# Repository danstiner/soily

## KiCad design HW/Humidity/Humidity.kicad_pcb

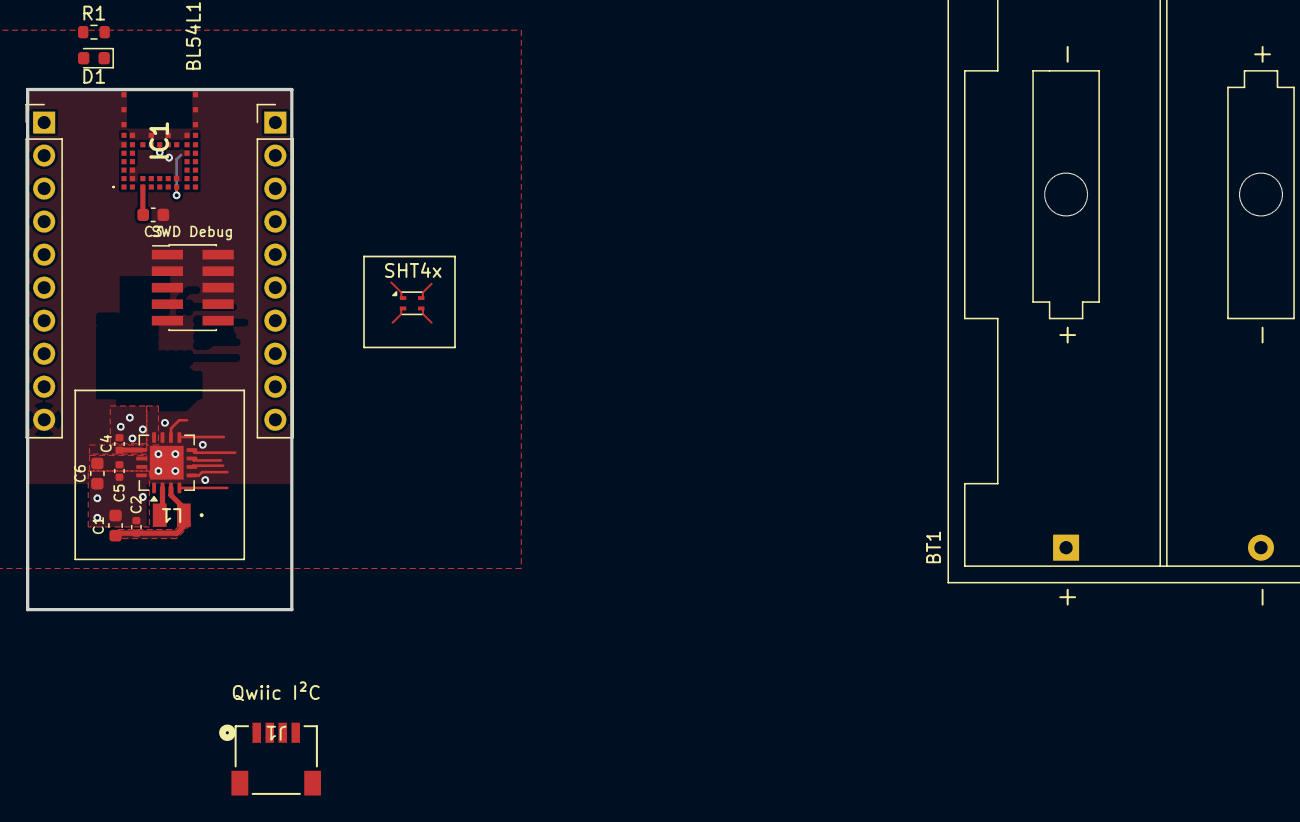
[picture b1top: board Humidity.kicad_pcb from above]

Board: 2 copper layers, 20.3 x 40.0 mm, 17 parts (0 on the bottom side), 15 nets.

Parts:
BT1: Battery; BatteryHolder_Keystone_2462_2xAA
C1, C6: 22μF; C_0603_1608Metric
C2, C5: 10nF; C_0402_1005Metric
C3: 10uF; C_0603_1608Metric
C4: 2.2μF; C_0402_1005Metric
D1: PWRLED; LED_0603_1608Metric
IC1: nrf54L 453-00223R; 45300223R
J1: Conn_Qwiic; CONN_SM04B-SRSS-TB_JST
J2: Conn_ARM_JTAG_SWD_10; PinHeader_2x05_P1.27mm_Vertical_SMD
J3, J4: Conn_01x10_Pin; PinHeader_1x10_P2.54mm_Vertical
L1: 2.2μH; IND_CIGT2016_SAM
R1: 2K; R_0603_1608Metric
U2: nPM2100-QEXX; UQFN-16-1EP_4x4mm_P0.65mm_EP2.6x2.6mm
U3: SHT4x; Sensirion_DFN-4_1.5x1.5mm_P0.8mm_SHT4x_NoCentralPad

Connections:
/LED: IC1.21 (P1.10), J4.5, R1.1
/NRESET: IC1.32 (NRESET), J2.10 (~RESET), J4.1
/PG/RESET: IC1.45 (P2.04), U2.10 (PG/RESET)
/SCL: IC1.17 (P1.04/AIN0/CLK), J1.4, J4.7, U2.7 (SCL), U3.2 (SCL)
/SDA: IC1.18 (P1.14), J1.3, J4.6, U2.6 (SDA), U3.1 (SDA)
/SW: L1.2, U2.2 (SW)
/SWDCLK: IC1.25 (SWDCLK), J2.4 (SWCLK/TCK), J4.3
/SWDIO: IC1.27 (SWDIO), J2.2 (SWDIO/TMS), J4.2
/SWO: IC1.13 (P2.02), J2.6 (SWO/TDO), J4.4
/VBAT: BT1.1 (+), C1.1, C2.1, L1.1, U2.3 (VBAT)
/VINT: C5.1, C6.1, U2.14 (VINT), U2.15 (VINT)
GND: BT1.2 (-), C1.2, C2.2, C3.2, C4.2, C5.2, C6.2, D1.1 (K), IC1.4 (GND_1), IC1.14 (GND_2), IC1.24 (GND_3), IC1.28 (GND_4), IC1.31 (GND_5), IC1.34 (GND_6), IC1.36 (GND_7), IC1.39 (GND_8), IC1.44 (P2.03), IC1.46 (GND_9), IC1.47 (GND_10), IC1.48 (GND_11), IC1.49 (GND_12), IC1.50 (GND_13), IC1.51 (GND_14), J1.1, J1.5 (MT1), J1.6 (MT2), J2.3 (GND), J2.5 (GND), J2.9 (GNDDetect), J3.10, U2.11 (AVSS2), U2.16 (PVSS), U2.17 (EP), U3.4 (VSS)
unnamed: D1.2 (A), R1.2
VDD: C3.1, C4.1, IC1.5 (VDD_NRF), J2.1 (VTref), U2.13 (VOUT)
VDDSW: J1.2, U2.12 (VOUTLDO), U3.3 (VDD)

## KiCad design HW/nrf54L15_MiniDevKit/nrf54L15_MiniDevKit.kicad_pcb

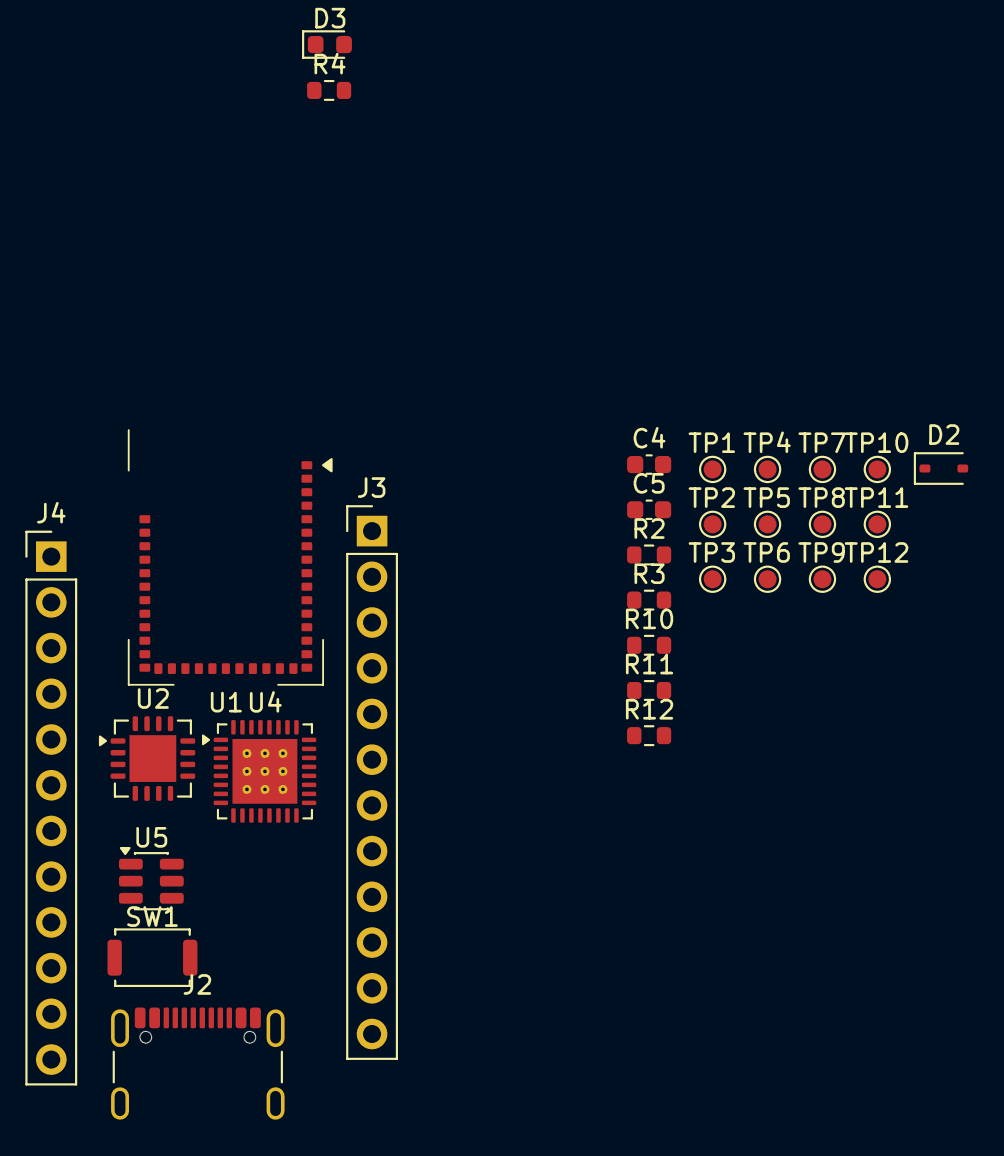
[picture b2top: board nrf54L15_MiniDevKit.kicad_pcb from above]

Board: 2 copper layers, 30 parts (0 on the bottom side), 14 nets, no tracks yet.

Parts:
C4, C5: 1u; C_0603_1608Metric
D2: B0520WS-7-F; D_SOD-323
D3: PWRLED; LED_0603_1608Metric
J2: USB4105-GF-A; USB_C_Receptacle_GCT_USB4105-xx-A_16P_TopMnt_Horizontal
J3, J4: Conn_Breadboard; PinHeader_1x12_P2.54mm_Vertical
R2, R3: 5.1k; R_0603_1608Metric
R4: 680; R_0603_1608Metric
R10: 60; R_0603_1608Metric
R11, R12: 10; R_0603_1608Metric
SW1: Reset; SW_Push_SPST_NO_Alps_SKRK
TP1: 3.3V; TestPoint_Pad_D1.0mm
TP2: GND; TestPoint_Pad_D1.0mm
TP3: BOOT; TestPoint_Pad_D1.0mm
TP4: RST; TestPoint_Pad_D1.0mm
TP5: UART_TX; TestPoint_Pad_D1.0mm
TP6: UART_RX; TestPoint_Pad_D1.0mm
TP7: SCL; TestPoint_Pad_D1.0mm
TP8: SDA; TestPoint_Pad_D1.0mm
TP9: SOIL_A; TestPoint_Pad_D1.0mm
TP10: EOH; TestPoint_Pad_D1.0mm
TP11: FDC_OFF; TestPoint_Pad_D1.0mm
TP12: SOIL_B; TestPoint_Pad_D1.0mm
U1: BL54L15-453-000xxx; BL54Lxx-LGA-39_14x10mm
U2: nPM2100-QEXX; UQFN-16-1EP_4x4mm_P0.65mm_EP2.6x2.6mm
U4: nPM1300-QEXX; QFN-32-1EP_5x5mm_P0.5mm_EP3.6x3.6mm_ThermalVias
U5: USBLC6-2SC6; SOT-23-6

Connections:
+3.3V: C5.1, J4.4, R4.1, TP1.1
/D+: J2.A6 (D+), J2.B6 (D+), U5.3 (I/O2)
/D-: J2.A7 (D-), J2.B7 (D-), U5.1 (I/O1)
/EOH: J4.8, TP10.1
/RESET: SW1.1, TP4.1
/SCL: J4.7, TP7.1
/SDA: J4.6, TP8.1
/USB_VBUS: D2.2 (A), J2.A4 (VBUS), J2.A9 (VBUS), J2.B4 (VBUS), J2.B9 (VBUS), U5.5 (VBUS)
GND: C4.2, C5.2, D3.1 (K), J2.A1 (GND), J2.A12 (GND), J2.B1 (GND), J2.B12 (GND), J2.S1 (SHIELD), J4.5, R2.1, R3.2, R10.2, R11.2, R12.2, SW1.2, TP2.1, U1.1 (VSS), U1.16 (VSS), U1.27 (VSS), U1.39 (VSS), U2.11 (AVSS2), U2.16 (PVSS), U2.17 (EP), U4.33 (AVSS), U5.2 (GND)
unnamed: C4.1, D2.1 (K)
unnamed: D3.2 (A), R4.2
unnamed: J2.A5 (CC1), R2.2
unnamed: J2.B5 (CC2), R3.1
unnamed: U2.14 (VINT), U2.15 (VINT)

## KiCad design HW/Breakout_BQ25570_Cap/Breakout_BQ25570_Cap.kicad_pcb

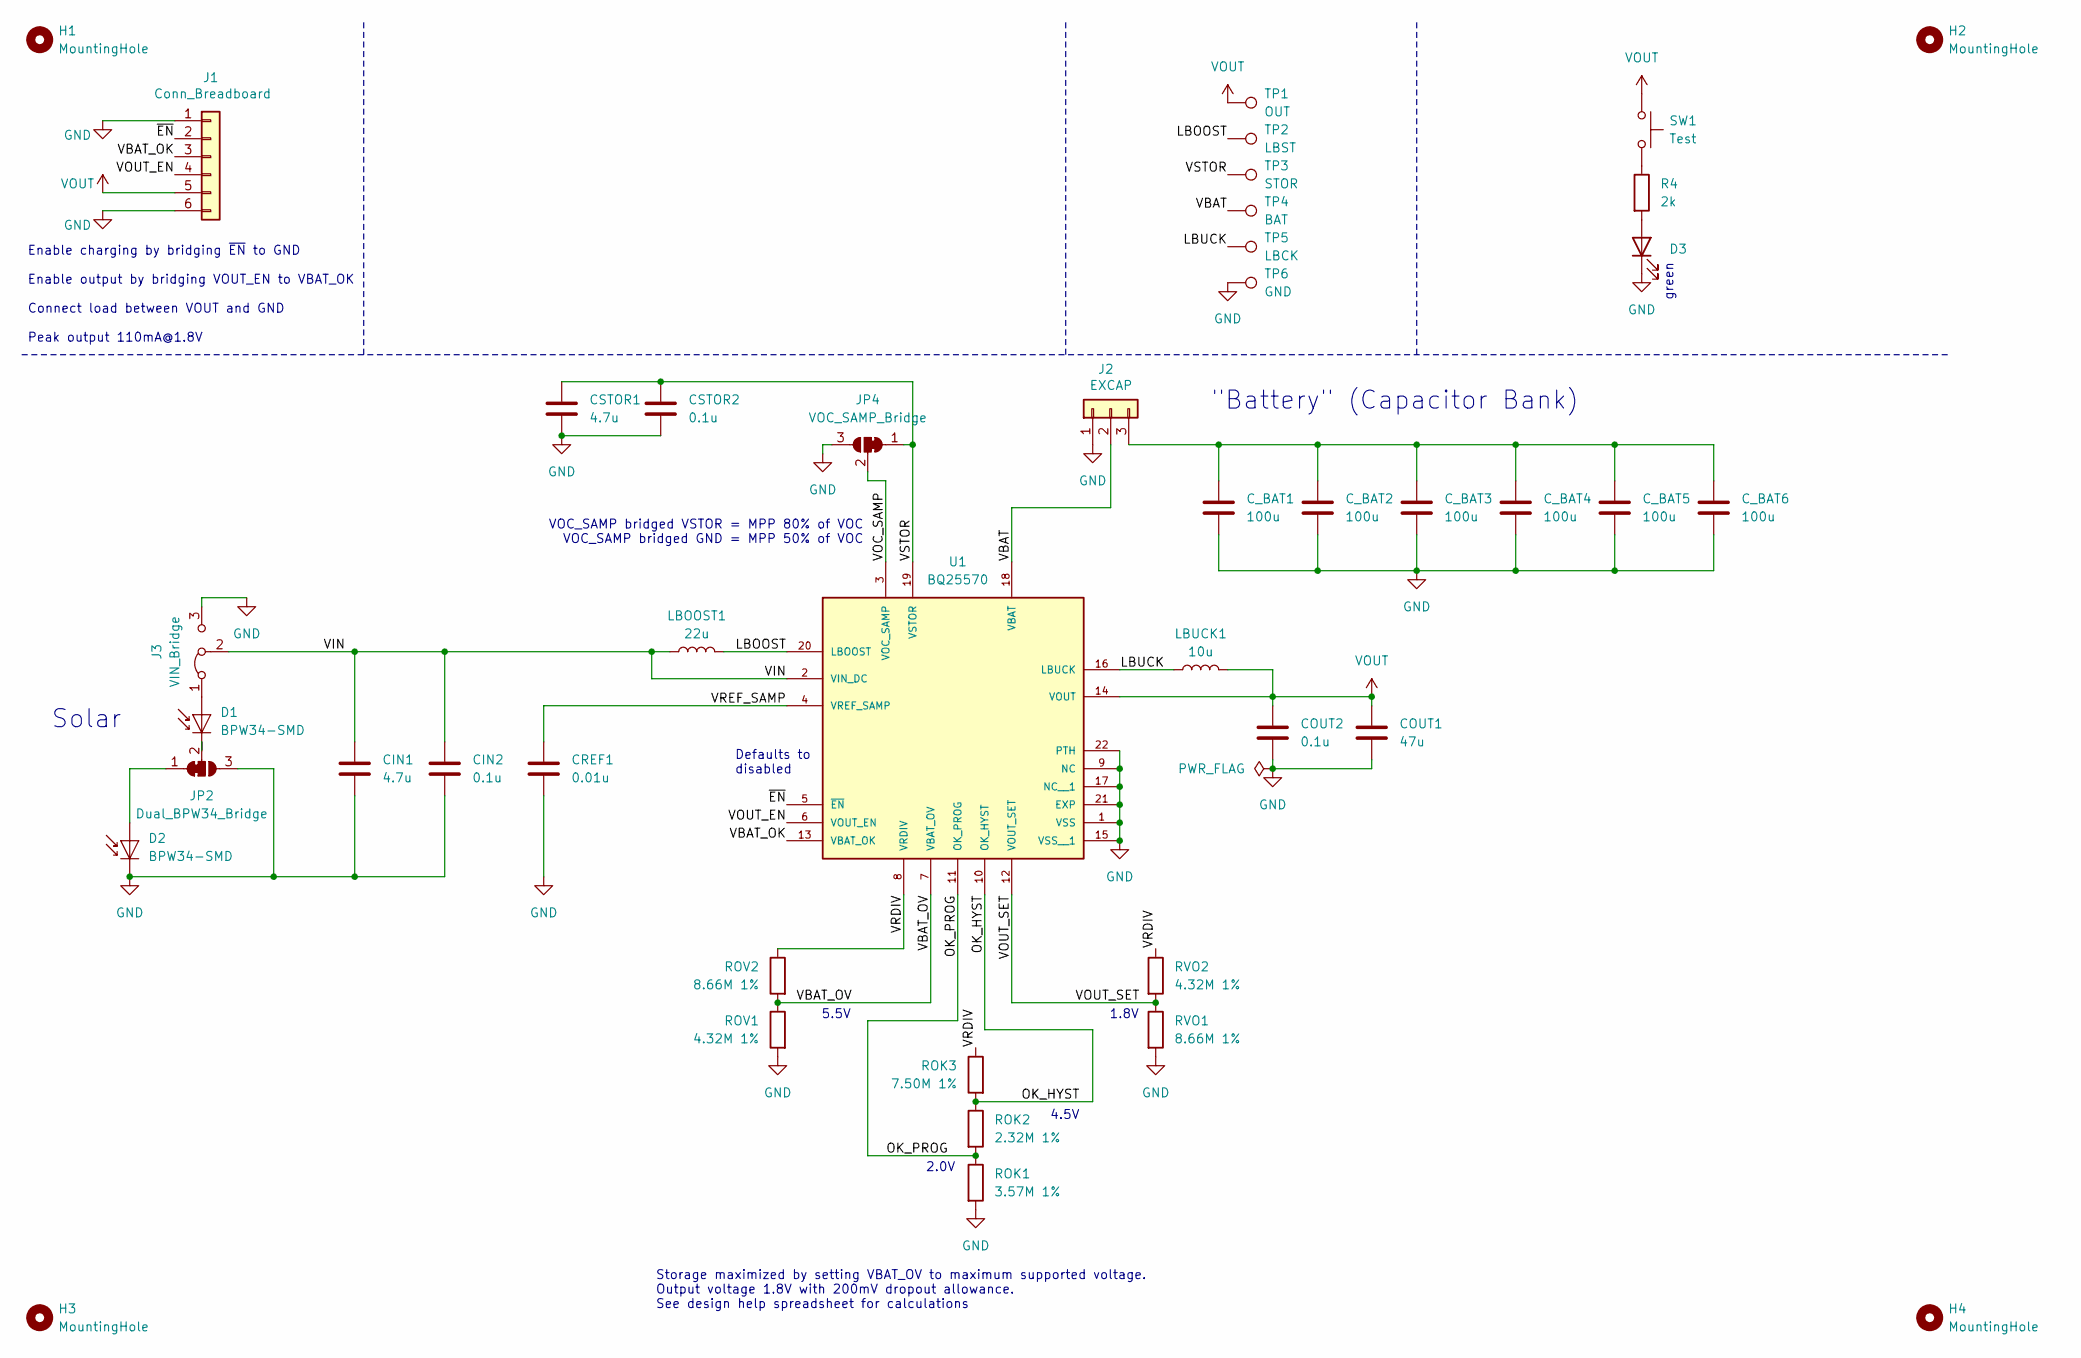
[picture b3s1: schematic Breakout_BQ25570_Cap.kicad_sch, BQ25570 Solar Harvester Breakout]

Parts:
CIN1: 4.7u; C_0603_1608Metric
CIN2: 0.1u; C_0402_1005Metric
COUT1: 47u; C_0603_1608Metric
COUT2: 0.1u; C_0402_1005Metric
CREF1: 0.01u; C_0402_1005Metric; Digikey Part Number 1276-1028-1-ND
CSTOR1: 4.7u; C_0603_1608Metric
CSTOR2: 0.1u; C_0402_1005Metric
C_BAT1: 100u; C_1206_3216Metric; Digikey Part Number 490-GRM31CR61A107MEA8LCT-ND
C_BAT2, C_BAT3, C_BAT4, C_BAT5, C_BAT6: 100u; C_1206_3216Metric
D1, D2: BPW34-SMD; Osram_BPW34S-SMD
D3: PWRLED; LED_0603_1608Metric
H1, H2, H3, H4: MountingHole; MountingHole_2.5mm_Plated
J1: Conn_Breadboard; PinHeader_1x06_P2.54mm_Vertical
J2: EXCAP; PinHeader_1x03_P2.54mm_Vertical
J3: VIN_Bridge; PinHeader_1x03_P2.54mm_Vertical
JP2: Dual_BPW34_Bridge; SolderJumper-3_P1.3mm_Bridged12_RoundedPad1.0x1.5mm
JP4: VOC_SAMP_Bridge; SolderJumper-3_P1.3mm_Bridged12_RoundedPad1.0x1.5mm
LBOOST1: 22u; L_Bourns-SRN4018; Digikey Part Number 118-SRN2012T-220KCT-ND
LBUCK1: 10u; L_1008_2520Metric; Digikey Part Number 490-10563-1-ND
R4: 2k; R_0603_1608Metric; Digikey Part Number 13-RC0603FR-101KLCT-ND
ROK1: 3.57M 1%; R_0603_1608Metric
ROK2: 2.32M 1%; R_0603_1608Metric
ROK3: 7.50M 1%; R_0603_1608Metric
ROV1: 4.32M 1%; R_0603_1608Metric
ROV2: 8.66M 1%; R_0603_1608Metric
RVO1: 8.66M 1%; R_0603_1608Metric
RVO2: 4.32M 1%; R_0603_1608Metric
SW1: Test; SW_Push_SPST_NO_Alps_SKRK; Part Number SKRKAHE020; Digikey Part Number 4809-SKRKAHE020CT-ND
TP1: OUT; TestPoint_Pad_D1.0mm
TP2: LBST; TestPoint_Pad_D1.0mm
TP3: STOR; TestPoint_Pad_D1.0mm
TP4: BAT; TestPoint_Pad_D1.0mm
TP5: LBCK; TestPoint_Pad_D1.0mm
TP6: GND; TestPoint_Pad_D1.0mm
U1: BQ25570; QFN50P350X350X100-21N; PARTREV G

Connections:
/LBOOST: LBOOST1.2, TP2.1, U1.20 (LBOOST)
/LBUCK: LBUCK1.1, TP5.1, U1.16 (LBUCK)
/OK_HYST: ROK2.1, ROK3.2, U1.10 (OK_HYST)
/OK_PROG: ROK1.1, ROK2.2, U1.11 (OK_PROG)
/VBAT: J2.2, TP4.1, U1.18 (VBAT)
/VBAT_OK: J1.3, U1.13 (VBAT_OK)
/VBAT_OV: ROV1.1, ROV2.2, U1.7 (VBAT_OV)
/VIN: CIN1.1, CIN2.1, J3.2 (C), LBOOST1.1, U1.2 (VIN_DC)
/VOC_SAMP: JP4.2 (C), U1.3 (VOC_SAMP)
/VOUT_EN: J1.4, U1.6 (VOUT_EN)
/VOUT_SET: RVO1.1, RVO2.2, U1.12 (VOUT_SET)
/VRDIV: ROK3.1, ROV2.1, RVO2.1, U1.8 (VRDIV)
/VREF_SAMP: CREF1.1, U1.4 (VREF_SAMP)
/VSTOR: CSTOR1.1, CSTOR2.1, JP4.1 (A), TP3.1, U1.19 (VSTOR)
/~EN: J1.2, U1.5 (~EN)
GND: CIN1.2, CIN2.2, COUT1.2, COUT2.2, CREF1.2, CSTOR1.2, CSTOR2.2, C_BAT1.2, C_BAT2.2, C_BAT3.2, C_BAT4.2, C_BAT5.2, C_BAT6.2, D2.1 (K), D3.1 (K), J1.1, J1.6, J2.1, J3.3 (B), JP2.3 (B), JP4.3 (B), ROK1.2, ROV1.2, RVO1.2, TP6.1, U1.1 (VSS), U1.9 (NC), U1.15 (VSS__1), U1.17 (NC__1), U1.21 (EXP), U1.22 (PTH), U1.23 (PTH), U1.24 (PTH), U1.25 (PTH), U1.26 (PTH)
unnamed: D1.2 (A), J3.1 (A)
unnamed: D1.1 (K), JP2.2 (C)
unnamed: D2.2 (A), JP2.1 (A)
unnamed: D3.2 (A), R4.2
unnamed: C_BAT1.1, C_BAT2.1, C_BAT3.1, C_BAT4.1, C_BAT5.1, C_BAT6.1, J2.3
unnamed: R4.1, SW1.2
VOUT: COUT1.1, COUT2.1, J1.5, LBUCK1.2, SW1.1, TP1.1, U1.14 (VOUT)

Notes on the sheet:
1.8V
Solar
Defaults to disabled
VOC_SAMP bridged VSTOR = MPP 80% of VOC VOC_SAMP bridged GND = MPP 50% of VOC
Enable charging by bridging ~{EN} to GND Enable output by bridging VOUT_EN to VBAT_OK Connect load between VOUT and GND Peak output 110mA@1.8V
2.0V
green
"Battery" (Capacitor Bank)
Storage maximized by setting VBAT_OV to maximum supported voltage. Output voltage 1.8V with 200mV dropout allowance. See design help spreadsheet for calculations
5.5V
4.5V

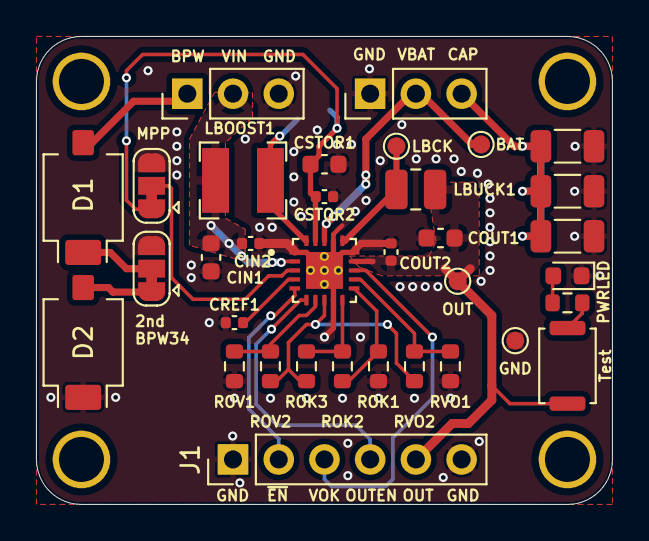
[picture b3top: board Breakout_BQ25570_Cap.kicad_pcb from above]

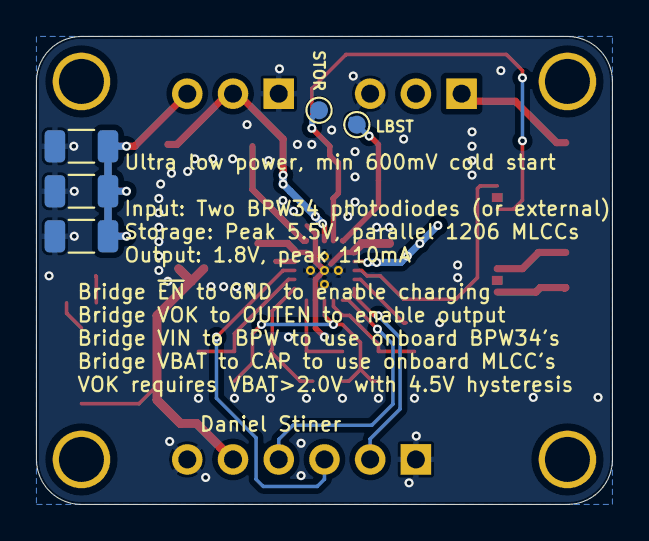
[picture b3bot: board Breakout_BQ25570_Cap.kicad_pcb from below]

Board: 2 copper layers, 32.0 x 26.0 mm, 43 parts (5 on the bottom side), 23 nets.

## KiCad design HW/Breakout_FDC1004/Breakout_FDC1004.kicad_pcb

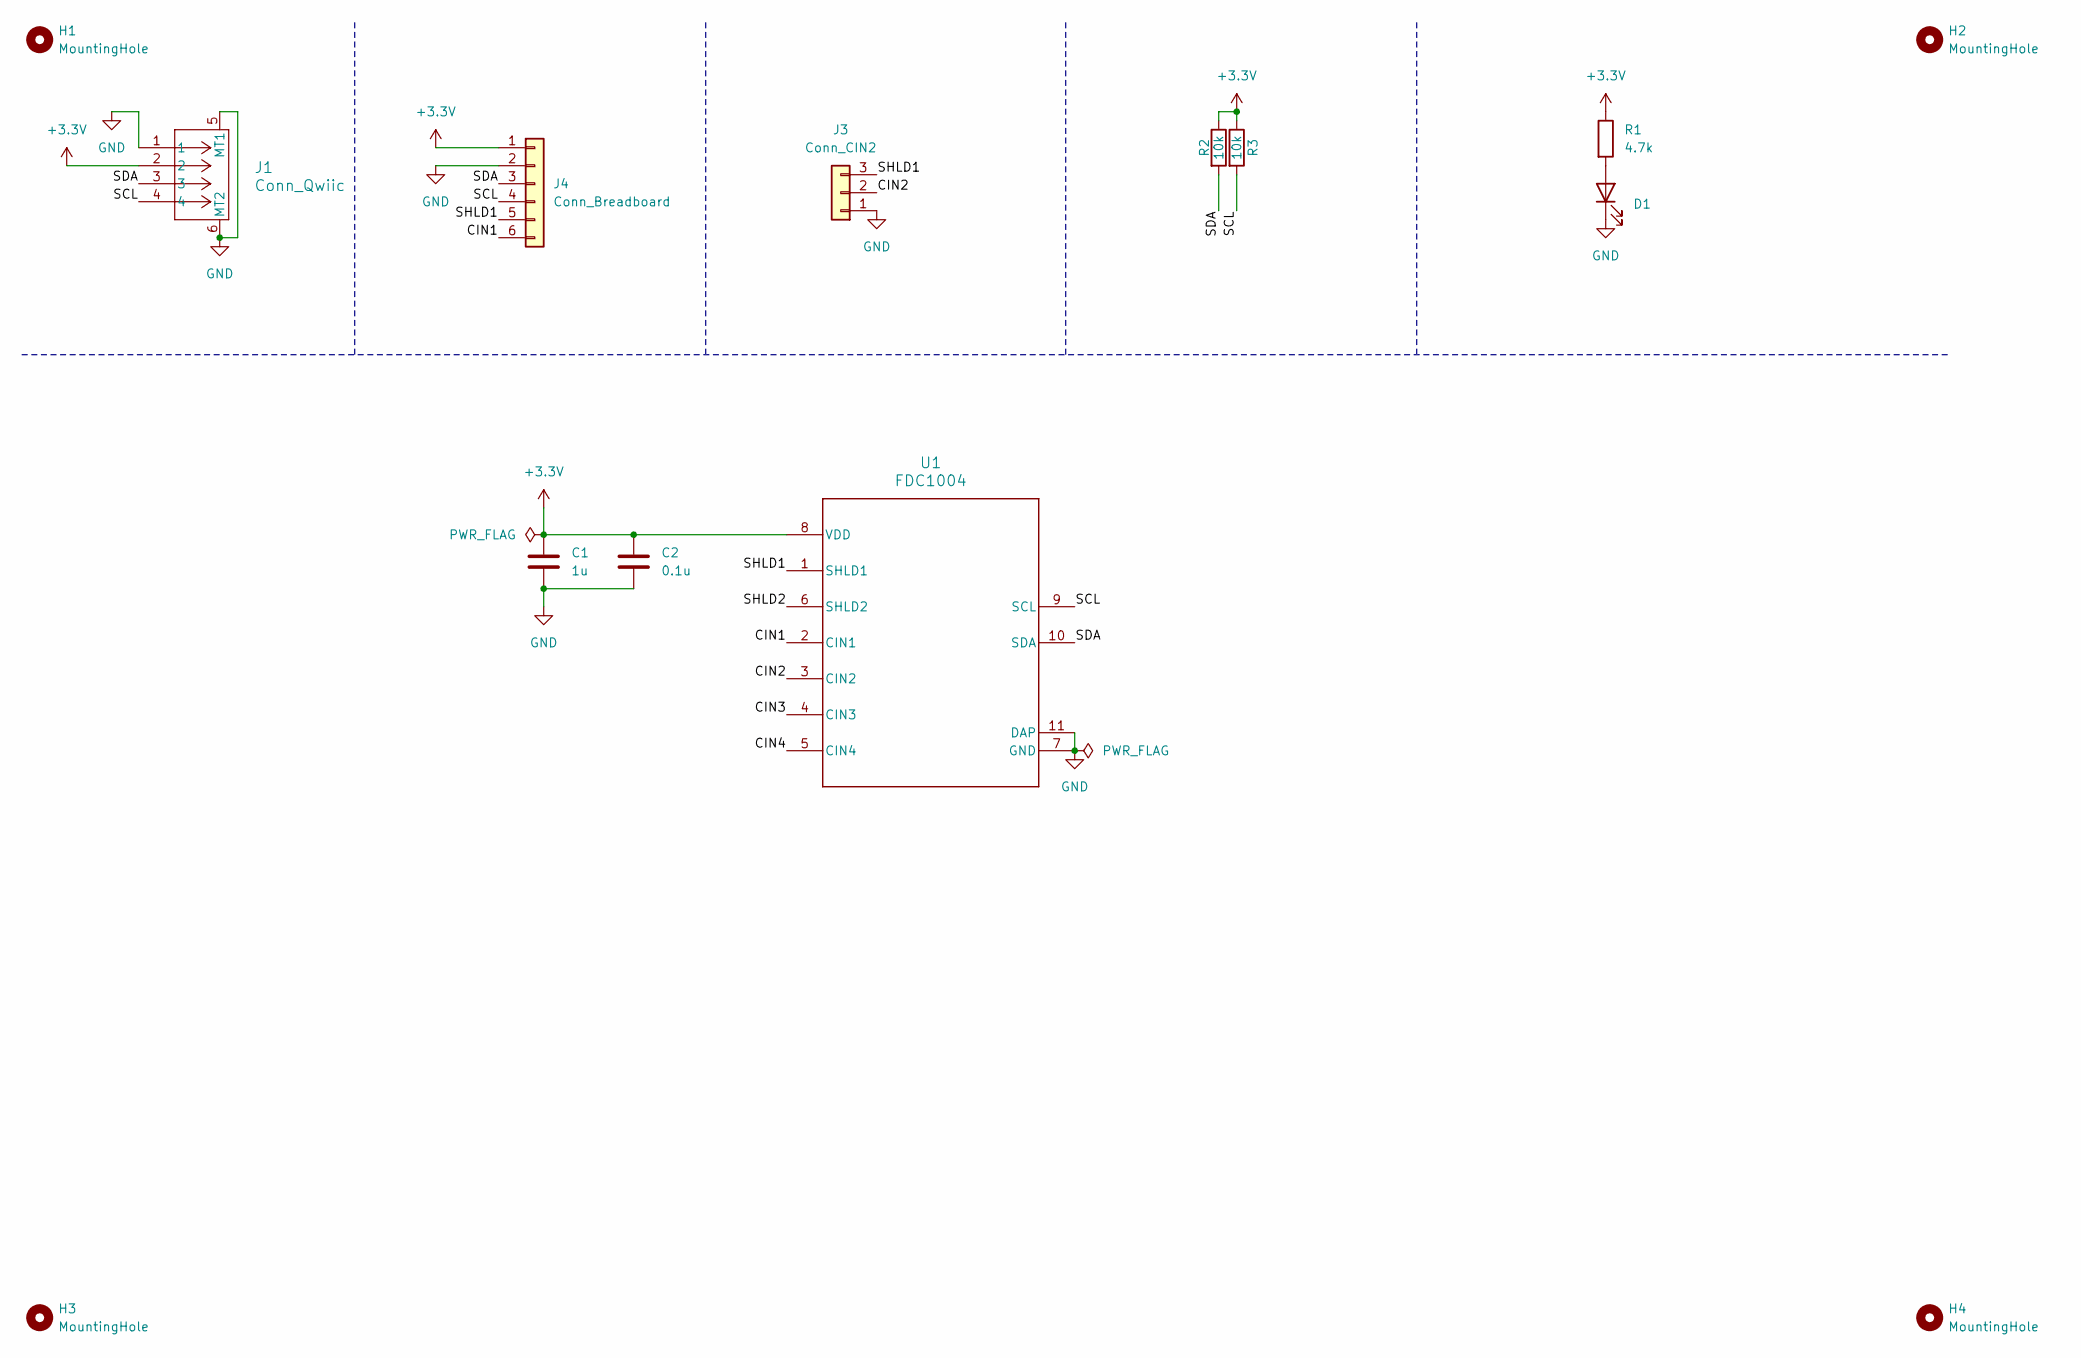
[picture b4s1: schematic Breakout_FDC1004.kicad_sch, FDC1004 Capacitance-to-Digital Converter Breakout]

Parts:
C1: 1u; C_0603_1608Metric
C2: 0.1u; C_0402_1005Metric
D1: PWRLED; LED_0603_1608Metric
H1, H2, H3, H4: MountingHole; MountingHole_2.5mm_Plated
J1: Conn_Qwiic; CONN_SM04B-SRSS-TB_JST
J3: Conn_CIN2; PinHeader_1x03_P2.54mm_Vertical
J4: Conn_Breadboard; PinHeader_1x06_P2.54mm_Vertical
R1: 4.7k; R_0603_1608Metric
R2, R3: 10k; R_0603_1608Metric; Digikey Part Number 311-10.0KHRCT-ND
U1: FDC1004; DSC0010B

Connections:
+3.3V: C1.1, C2.1, J1.2, J4.1, R1.1, R2.1, R3.1, U1.8 (VDD)
/CIN1: J4.6, U1.2 (CIN1)
/CIN2: J3.2, U1.3 (CIN2)
/CIN3: U1.4 (CIN3)
/CIN4: U1.5 (CIN4)
/SCL: J1.4, J4.4, R3.2, U1.9 (SCL)
/SDA: J1.3, J4.3, R2.2, U1.10 (SDA)
/SHLD1: J3.3, J4.5, U1.1 (SHLD1)
/SHLD2: U1.6 (SHLD2)
GND: C1.2, C2.2, D1.1 (K), J1.1, J1.5 (MT1), J1.6 (MT2), J3.1, J4.2, U1.7 (GND), U1.11 (DAP), U1.V (VIA)
unnamed: D1.2 (A), R1.2

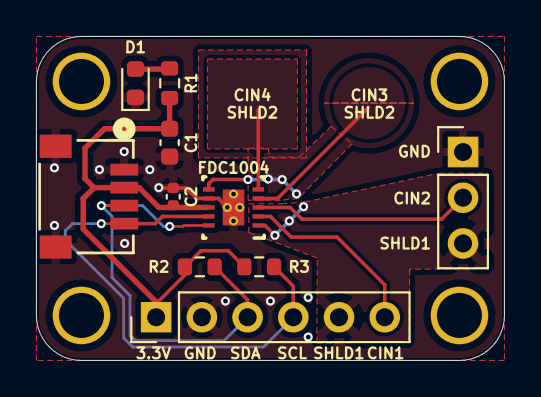
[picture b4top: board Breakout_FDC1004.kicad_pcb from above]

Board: 2 copper layers, 26.0 x 18.0 mm, 14 parts (0 on the bottom side), 8 nets.

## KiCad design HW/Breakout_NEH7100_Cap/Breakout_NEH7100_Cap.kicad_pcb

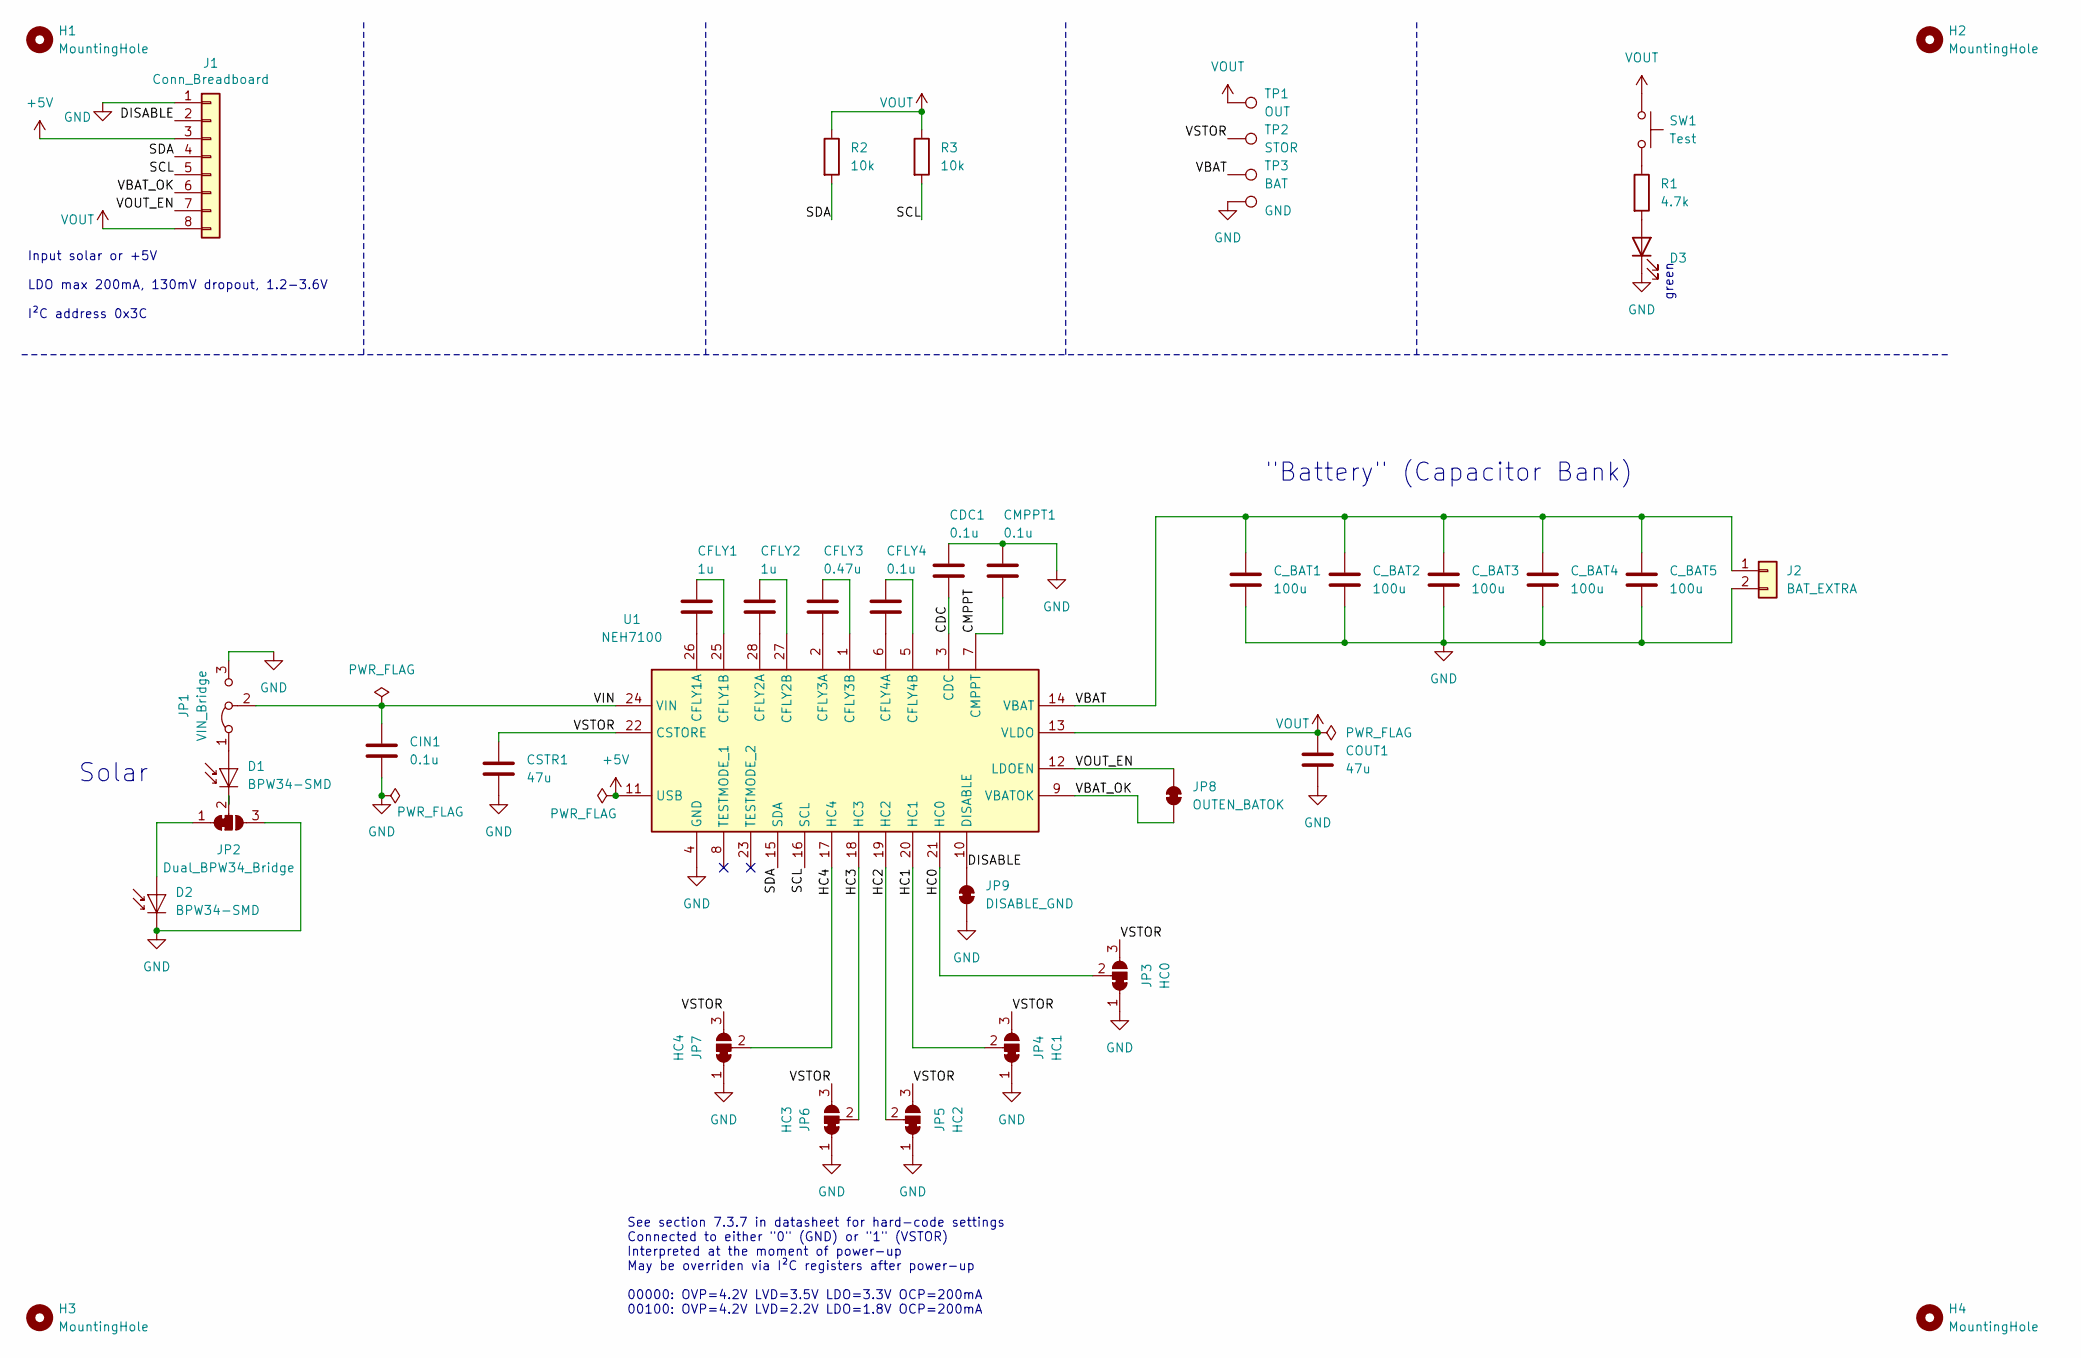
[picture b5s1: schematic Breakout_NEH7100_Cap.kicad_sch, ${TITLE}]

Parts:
CDC1: 0.1u; C_0402_1005Metric
CFLY1, CFLY2: 1u; C_0402_1005Metric
CFLY3: 0.47u; C_0402_1005Metric
CFLY4: 0.1u; C_0402_1005Metric
CIN1: 0.1u; C_0402_1005Metric
CMPPT1: 0.1u; C_0402_1005Metric
COUT1: 47u; C_0603_1608Metric
CSTR1: 47u; C_0603_1608Metric; Digikey Part Number 1276-1028-1-ND
C_BAT1: 100u; C_1206_3216Metric; Digikey Part Number 490-GRM31CR61A107MEA8LCT-ND
C_BAT2, C_BAT3, C_BAT4, C_BAT5: 100u; C_1206_3216Metric
D1, D2: BPW34-SMD; Osram_BPW34S-SMD
D3: PWRLED; LED_0603_1608Metric
H1, H2, H3, H4: MountingHole; MountingHole_2.5mm_Plated
J1: Conn_Breadboard; PinHeader_1x08_P2.54mm_Vertical
J2: BAT_EXTRA; PinHeader_1x02_P2.54mm_Vertical
JP1: VIN_Bridge; PinHeader_1x03_P2.54mm_Vertical
JP2: Dual_BPW34_Bridge; SolderJumper-3_P1.3mm_Bridged12_RoundedPad1.0x1.5mm
JP3: HC0; SolderJumper-3_P1.3mm_Bridged12_RoundedPad1.0x1.5mm
JP4: HC1; SolderJumper-3_P1.3mm_Bridged12_RoundedPad1.0x1.5mm
JP5: HC2; SolderJumper-3_P1.3mm_Bridged12_RoundedPad1.0x1.5mm
JP6: HC3; SolderJumper-3_P1.3mm_Bridged12_RoundedPad1.0x1.5mm
JP7: HC4; SolderJumper-3_P1.3mm_Bridged12_RoundedPad1.0x1.5mm
JP8: OUTEN_BATOK; SolderJumper-2_P1.3mm_Bridged_RoundedPad1.0x1.5mm
JP9: DISABLE_GND; SolderJumper-2_P1.3mm_Bridged_RoundedPad1.0x1.5mm
R1: 4.7k; R_0603_1608Metric; Digikey Part Number 13-RC0603FR-101KLCT-ND
R2, R3: 10k; R_0603_1608Metric
SW1: Test; SW_Push_SPST_NO_Alps_SKRK; Part Number SKRKAHE020; Digikey Part Number 4809-SKRKAHE020CT-ND
TP1: OUT; TestPoint_Pad_D1.0mm
TP2: STOR; TestPoint_Pad_D1.0mm
TP3: BAT; TestPoint_Pad_D1.0mm
TP6: GND; TestPoint_Pad_D1.0mm
U1: NEH7100; QFN40P400X400X90-29N-D; Mouser Part Number 771-NEH7100BUHP

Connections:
+5V: J1.3, U1.11 (USB)
/CDC: CDC1.2, U1.3 (CDC)
/CMPPT: CMPPT1.2, U1.7 (CMPPT)
/DISABLE: J1.2, JP9.2 (B), U1.10 (DISABLE)
/HC0: JP3.2 (C), U1.21 (HC0)
/HC1: JP4.2 (C), U1.20 (HC1)
/HC2: JP5.2 (C), U1.19 (HC2)
/HC3: JP6.2 (C), U1.18 (HC3)
/HC4: JP7.2 (C), U1.17 (HC4)
/SCL: J1.5, R3.2, U1.16 (SCL)
/SDA: J1.4, R2.2, U1.15 (SDA)
/VBAT: C_BAT1.1, C_BAT2.1, C_BAT3.1, C_BAT4.1, C_BAT5.1, J2.1, TP3.1, U1.14 (VBAT)
/VBAT_OK: J1.6, JP8.1 (A), U1.9 (VBATOK)
/VIN: CIN1.1, JP1.2 (C), U1.24 (VIN)
/VOUT_EN: J1.7, JP8.2 (B), U1.12 (LDOEN)
/VSTOR: CSTR1.1, JP3.3 (B), JP4.3 (B), JP5.3 (B), JP6.3 (B), JP7.3 (B), TP2.1, U1.22 (CSTORE)
GND: CDC1.1, CIN1.2, CMPPT1.1, COUT1.2, CSTR1.2, C_BAT1.2, C_BAT2.2, C_BAT3.2, C_BAT4.2, C_BAT5.2, D2.1 (K), D3.1 (K), J1.1, J2.2, JP1.3 (B), JP2.3 (B), JP3.1 (A), JP4.1 (A), JP5.1 (A), JP6.1 (A), JP7.1 (A), JP9.1 (A), TP6.1, U1.4 (GND), U1.29 (GND_2)
unnamed: D1.2 (A), JP1.1 (A)
unnamed: D1.1 (K), JP2.2 (C)
unnamed: D2.2 (A), JP2.1 (A)
unnamed: D3.2 (A), R1.2
unnamed: R1.1, SW1.2
unnamed: CFLY1.2, U1.26 (CFLY1A)
unnamed: CFLY1.1, U1.25 (CFLY1B)
unnamed: CFLY2.2, U1.28 (CFLY2A)
unnamed: CFLY2.1, U1.27 (CFLY2B)
unnamed: CFLY3.2, U1.2 (CFLY3A)
unnamed: CFLY3.1, U1.1 (CFLY3B)
unnamed: CFLY4.2, U1.6 (CFLY4A)
unnamed: CFLY4.1, U1.5 (CFLY4B)
VOUT: COUT1.1, J1.8, R2.1, R3.1, SW1.1, TP1.1, U1.13 (VLDO)

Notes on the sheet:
Solar
Input solar or +5V LDO max 200mA, 130mV dropout, 1.2-3.6V I²C address 0x3C
See section 7.3.7 in datasheet for hard-code settings Connected to either "0" (GND) or "1" (VSTOR) Interpreted at the moment of power-up May be overriden via I²C registers after power-up 00000: OVP=4.2V LVD=3.5V LDO=3.3V OCP=200mA 00100: OVP=4.2V LVD=2.2V LDO=1.8V OCP=200mA
green
"Battery" (Capacitor Bank)

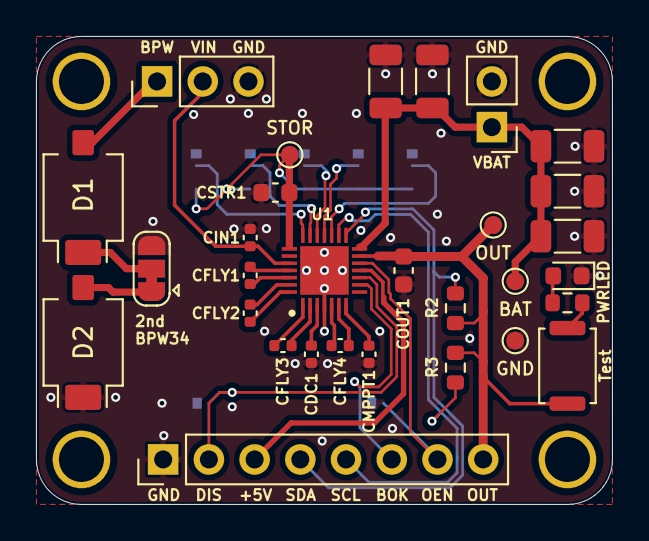
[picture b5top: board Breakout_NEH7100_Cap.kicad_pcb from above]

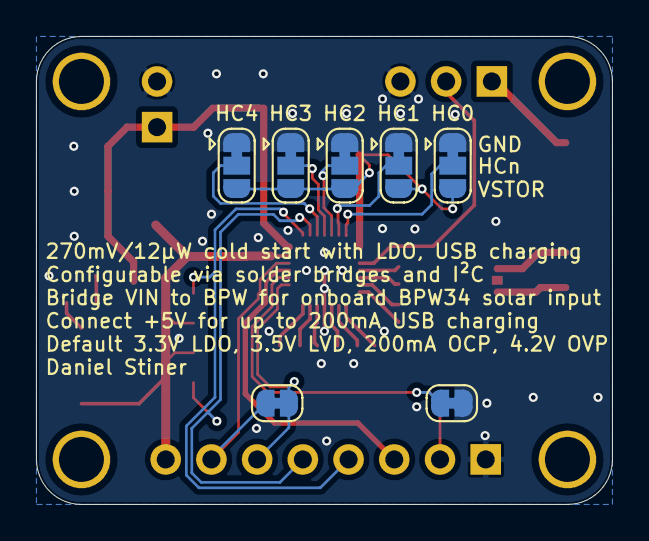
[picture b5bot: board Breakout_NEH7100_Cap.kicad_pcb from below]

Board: 2 copper layers, 32.0 x 26.0 mm, 41 parts (7 on the bottom side), 31 nets.

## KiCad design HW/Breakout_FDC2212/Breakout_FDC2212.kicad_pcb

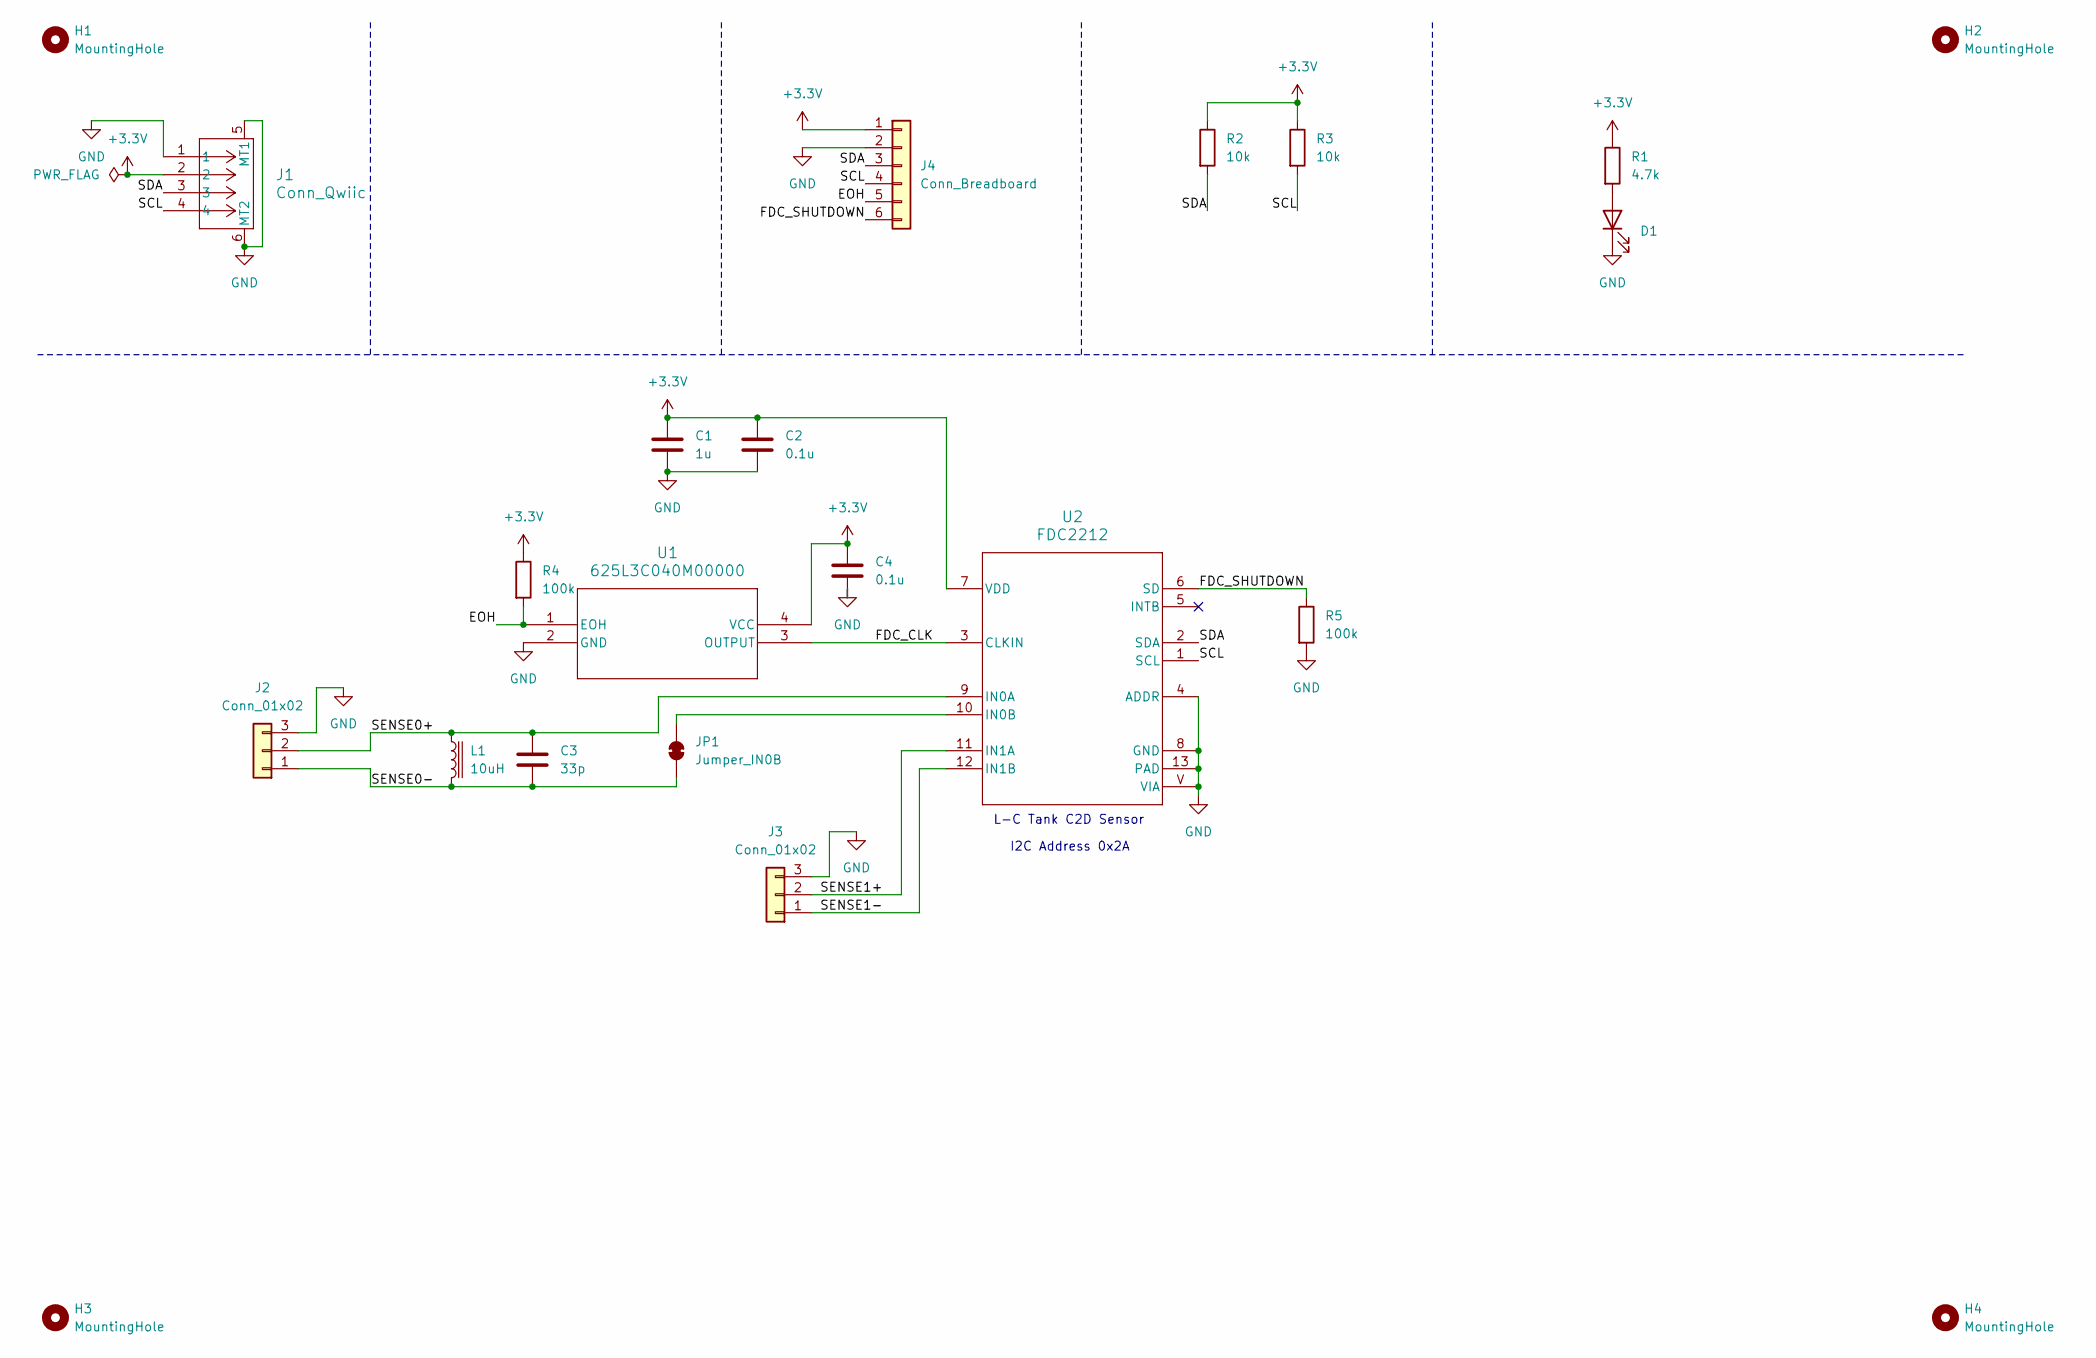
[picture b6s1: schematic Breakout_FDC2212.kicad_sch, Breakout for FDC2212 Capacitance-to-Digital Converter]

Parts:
C1: 1u; C_0603_1608Metric
C2, C4: 0.1u; C_0402_1005Metric; Digikey Part Number 490-5798-1-ND
C3: 33p; C_0603_1608Metric; Digikey Part Number 490-16409-1-ND
D1: PWRLED; LED_0603_1608Metric
H1, H2, H3, H4: MountingHole; MountingHole_2.5mm_Plated
J1: Conn_Qwiic; CONN_SM04B-SRSS-TB_JST
J2, J3: Conn_01x02; PinHeader_1x03_P2.54mm_Vertical
J4: Conn_Breadboard; PinHeader_1x06_P2.54mm_Vertical
JP1: Jumper_IN0B; SolderJumper-2_P1.3mm_Bridged_RoundedPad1.0x1.5mm
L1: 10uH; L_1210_3225Metric; Digikey Part Number 118-CMH322522-100KLCT-ND
R1: 4.7k; R_0603_1608Metric
R2, R3: 10k; R_0603_1608Metric
R4, R5: 100k; R_0603_1608Metric
U1: 625L3C040M00000; IC_625L3C040M00000_CTS; Digikey Part Number 110-625L3C040M00000CT-ND
U2: FDC2212; DNT0012B; Part Number FDC2212DNTT; Digikey Part Number 296-42304-1-ND

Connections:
+3.3V: C1.1, C2.1, C4.1, J1.2, J4.1, R1.1, R2.1, R3.1, R4.1, U1.4 (VCC), U2.7 (VDD)
/EOH: J4.5, R4.2, U1.1 (EOH)
/FDC_CLK: U1.3 (OUTPUT), U2.3 (CLKIN)
/FDC_SHUTDOWN: J4.6, R5.1, U2.6 (SD)
/SCL: J1.4, J4.4, R3.2, U2.1 (SCL)
/SDA: J1.3, J4.3, R2.2, U2.2 (SDA)
/SENSE0+: C3.1, J2.2, L1.1, U2.9 (IN0A)
/SENSE0-: C3.2, J2.1, JP1.2 (B), L1.2
/SENSE1+: J3.2, U2.11 (IN1A)
/SENSE1-: J3.1, U2.12 (IN1B)
GND: C1.2, C2.2, C4.2, D1.1 (K), J1.1, J1.5 (MT1), J1.6 (MT2), J2.3, J3.3, J4.2, R5.2, U1.2 (GND), U2.4 (ADDR), U2.8 (GND), U2.13 (PAD), U2.V (VIA)
unnamed: D1.2 (A), R1.2
unnamed: JP1.1 (A), U2.10 (IN0B)

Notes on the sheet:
L-C Tank C2D Sensor
I2C Address 0x2A
